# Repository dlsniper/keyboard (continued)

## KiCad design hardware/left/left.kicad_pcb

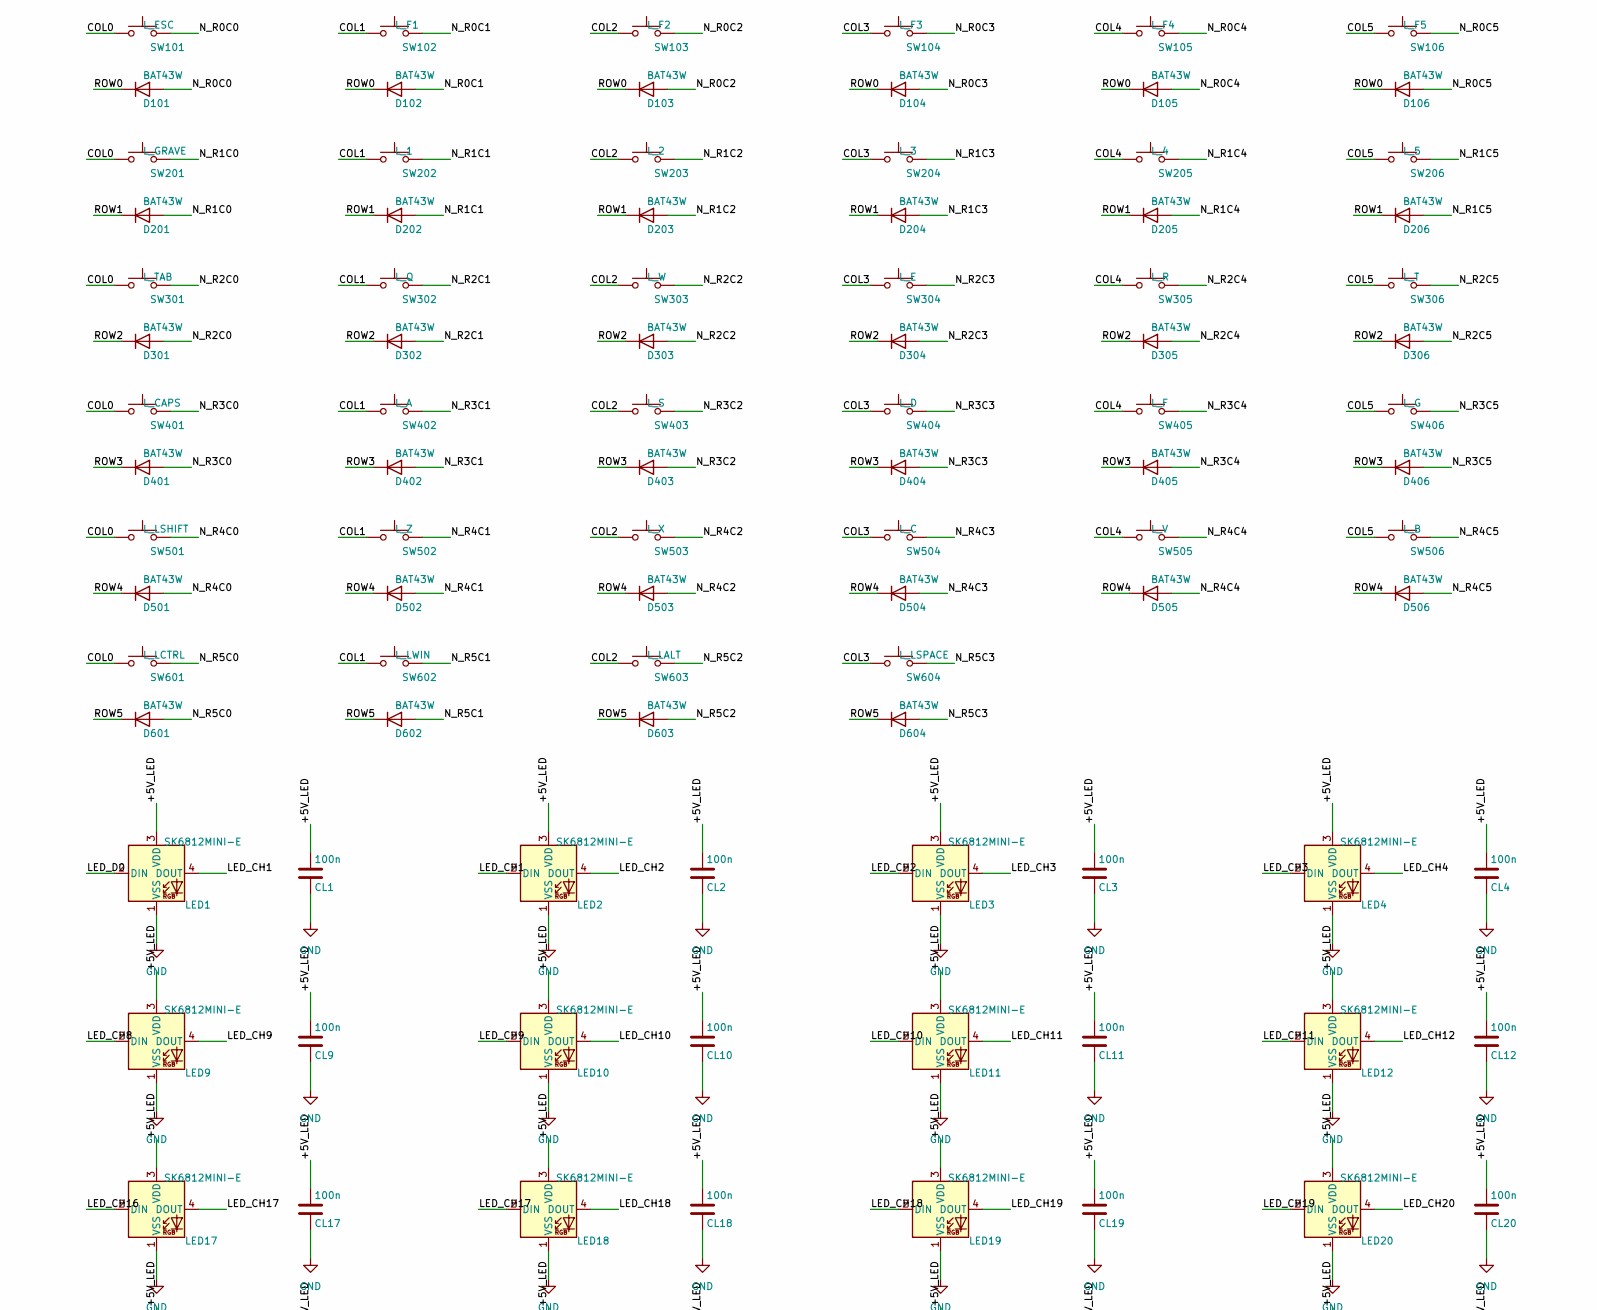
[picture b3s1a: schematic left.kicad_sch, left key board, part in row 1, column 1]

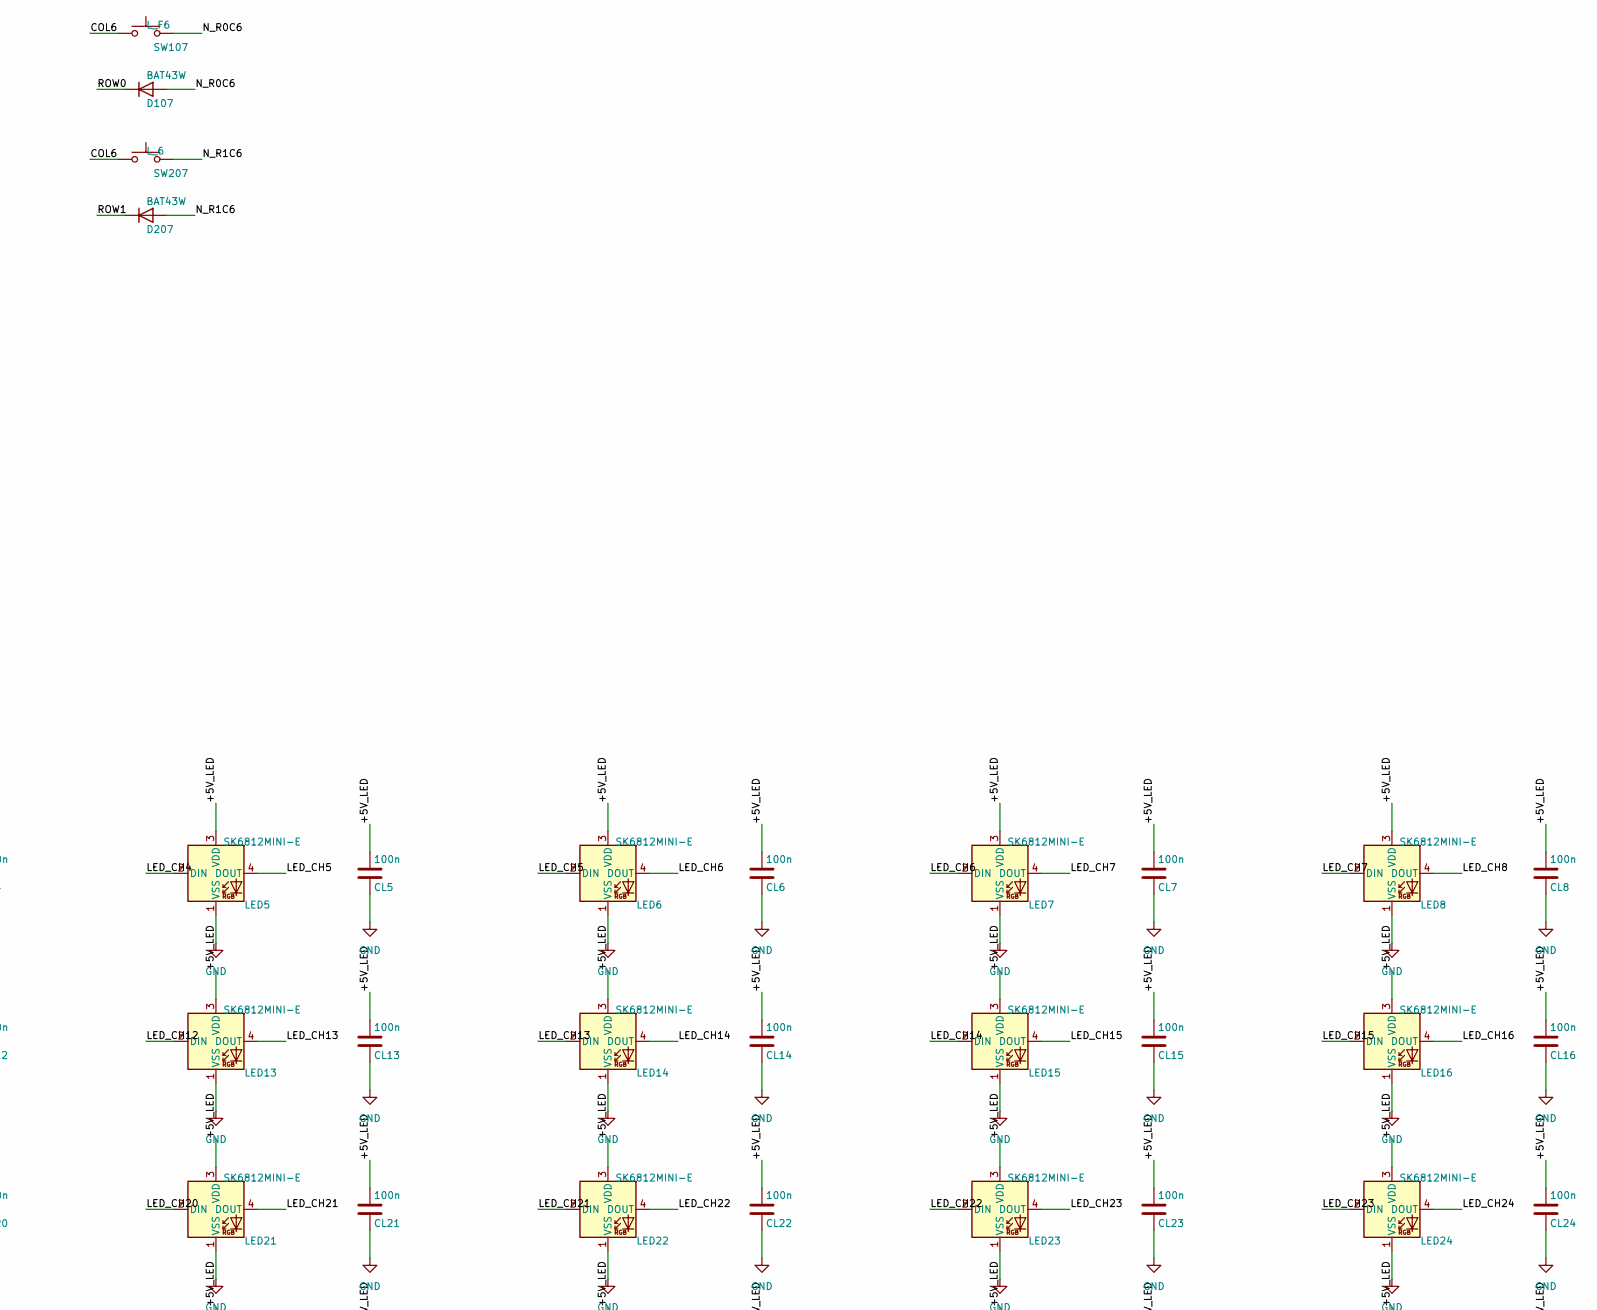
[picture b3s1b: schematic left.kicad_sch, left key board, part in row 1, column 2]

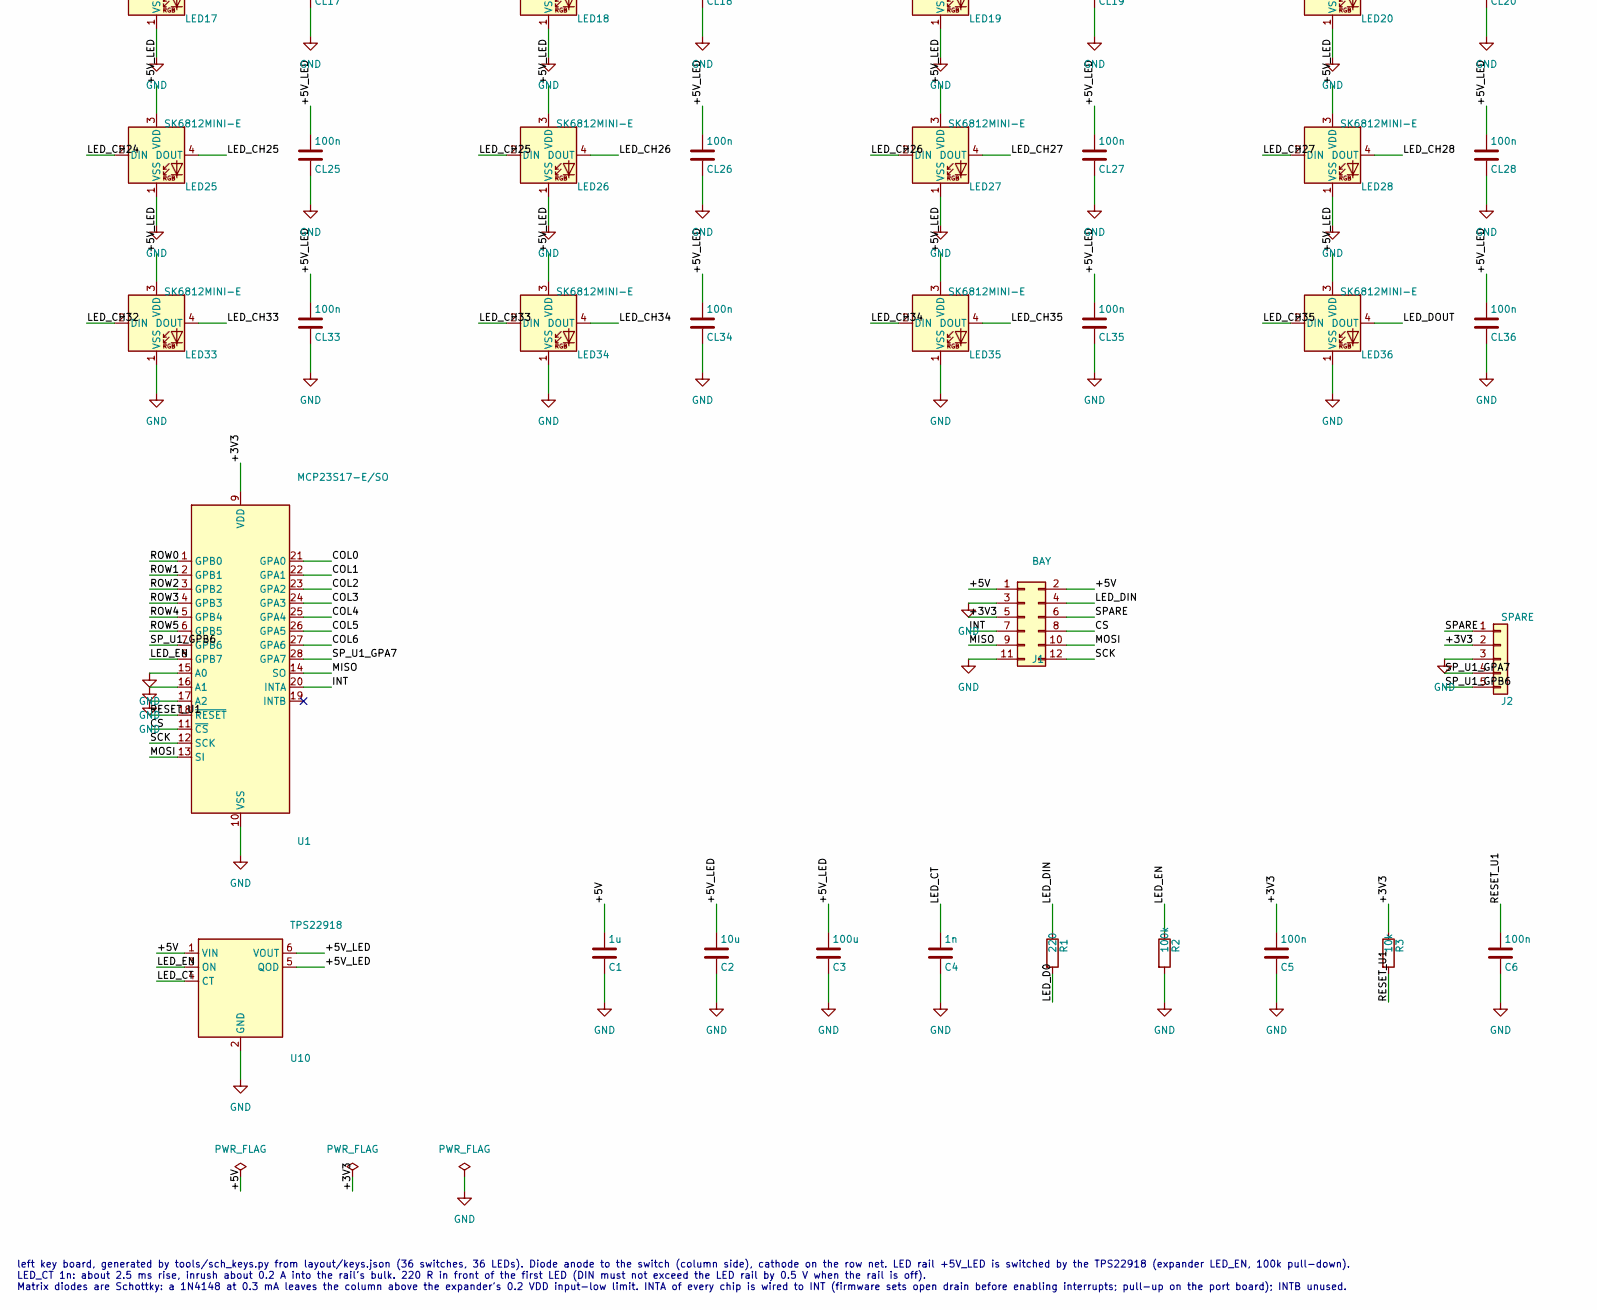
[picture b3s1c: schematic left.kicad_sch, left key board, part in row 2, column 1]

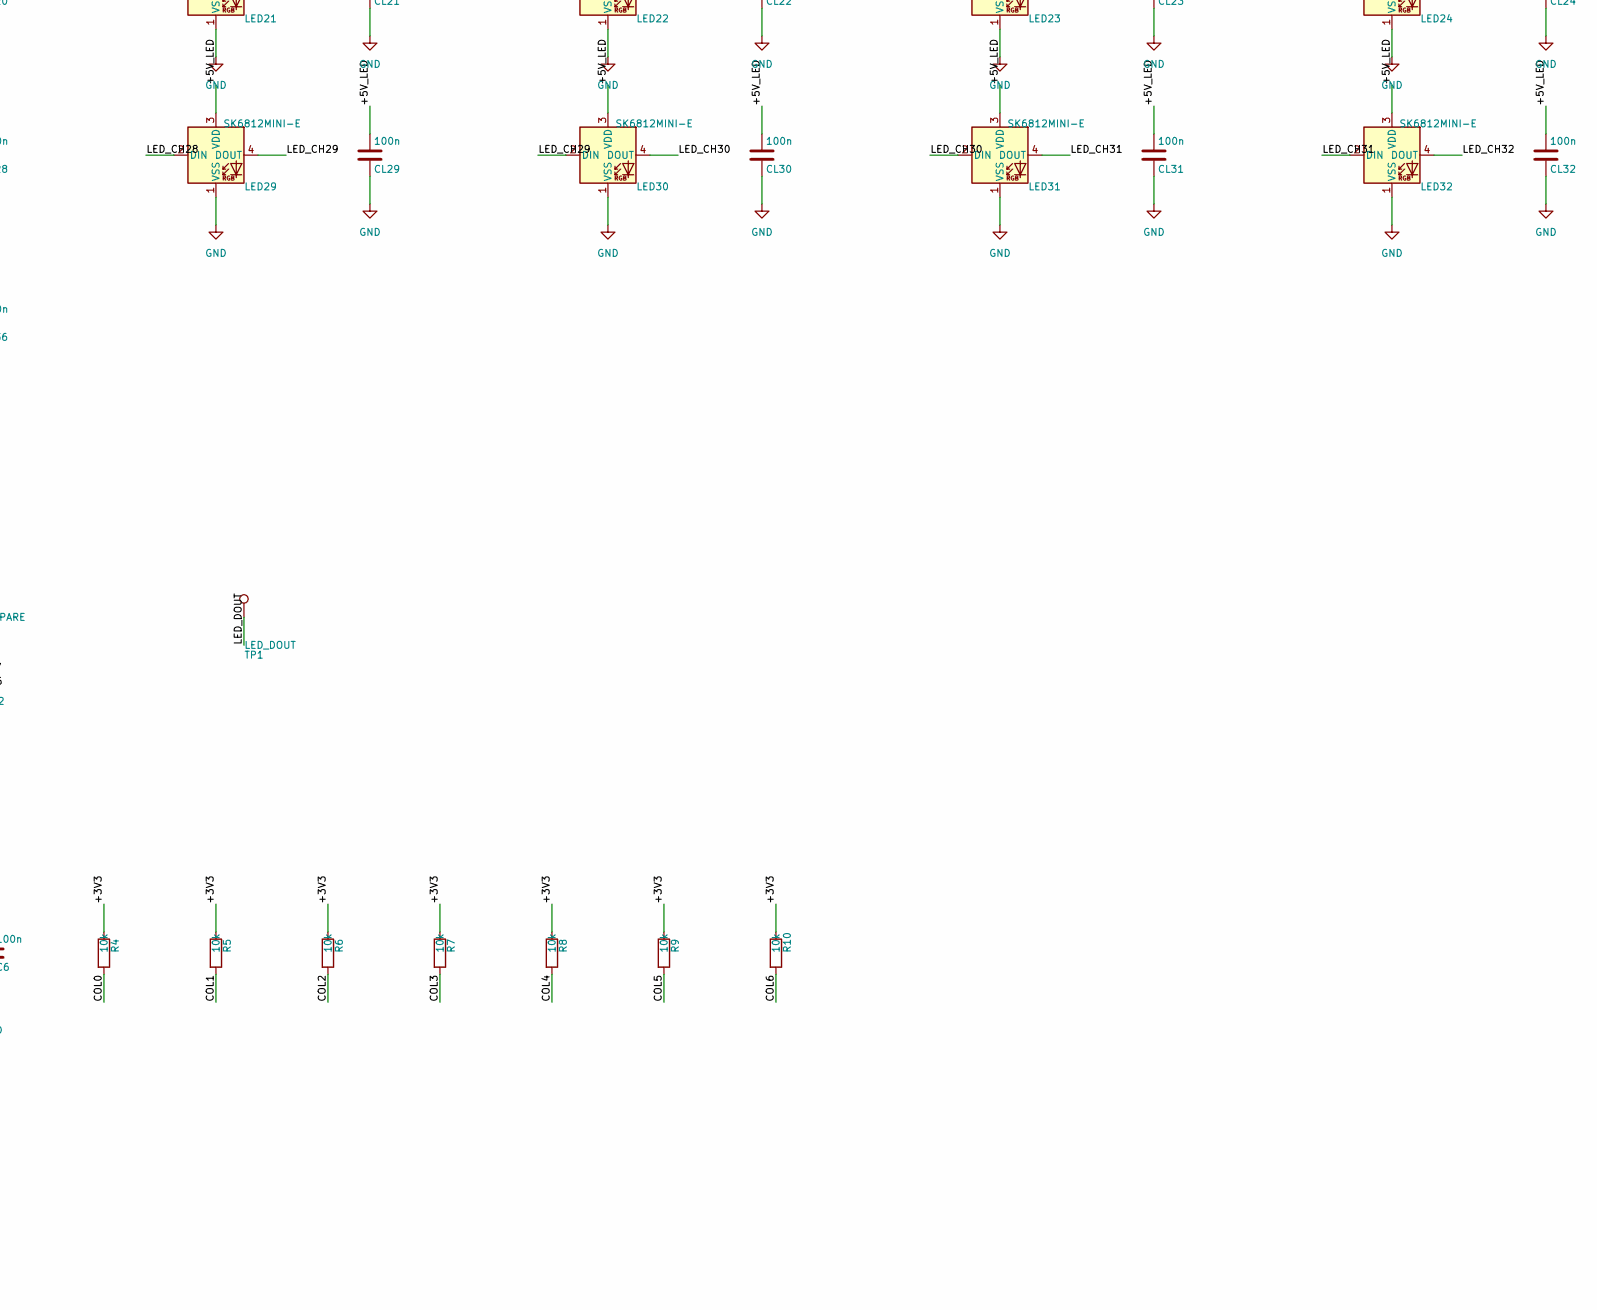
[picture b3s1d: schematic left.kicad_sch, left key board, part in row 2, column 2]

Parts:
C1: 1u; C_0805_2012Metric_Pad1.18x1.45mm_HandSolder; Voltage 16V
C2: 10u; C_0805_2012Metric_Pad1.18x1.45mm_HandSolder; Voltage 16V
C3: 100u; C_1210_3225Metric_Pad1.33x2.70mm_HandSolder; Voltage 10V
C4: 1n; C_0805_2012Metric_Pad1.18x1.45mm_HandSolder; Voltage 16V
C5, C6: 100n; C_0805_2012Metric_Pad1.18x1.45mm_HandSolder; Voltage 16V
CL1, CL2, CL3, CL4, CL5, CL6, CL7, CL8, CL9, CL10, CL11, CL12, CL13, CL14, CL15, CL16, CL17, CL18, CL19, CL20, CL21, CL22, CL23, CL24, CL25, CL26, CL27, CL28, CL29, CL30, CL31, CL32, CL33, CL34, CL35, CL36: 100n; C_0805_2012Metric_Pad1.18x1.45mm_HandSolder; Voltage 16V
D101, D102, D103, D104, D105, D106, D107, D201, D202, D203, D204, D205, D206, D207, D301, D302, D303, D304, D305, D306, D401, D402, D403, D404, D405, D406, D501, D502, D503, D504, D505, D506, D601, D602, D603, D604: BAT43W; D_SOD-123; MPN Schottky, SOD-123: BAT43W (VF 0.33 V ma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
J1: BAY; PinHeader_2x06_P2.54mm_Vertical; MPN generic 2x6 2.54 mm pin header
J2: SPARE; PinHeader_1x05_P2.54mm_Vertical; MPN generic 1xN 2.54 mm pin header
LED1, LED2, LED3, LED4, LED5, LED6, LED7, LED8, LED9, LED10, LED11, LED12, LED13, LED14, LED15, LED16, LED17, LED18, LED19, LED20, LED21, LED22, LED23, LED24, LED25, LED26, LED27, LED28, LED29, LED30, LED31, LED32, LED33, LED34, LED35, LED36: SK6812MINI-E; LED_SK6812MINI-E_3.2x2.8mm_P1.5mm_ReverseMount; MPN SK6812MINI-E
R1: 220; R_0805_2012Metric_Pad1.20x1.40mm_HandSolder; Tolerance 1%
R2: 100k; R_0805_2012Metric_Pad1.20x1.40mm_HandSolder; Tolerance 1%
R3, R4, R5, R6, R7, R8, R9, R10: 10k; R_0805_2012Metric_Pad1.20x1.40mm_HandSolder; Tolerance 1%
SW101: L_ESC; SW_Hotswap_Kailh_MX_1.00u; MPN Kailh CPG151101S11 hotswap socket
SW102: L_F1; SW_Hotswap_Kailh_MX_1.00u; MPN Kailh CPG151101S11 hotswap socket
SW103: L_F2; SW_Hotswap_Kailh_MX_1.00u; MPN Kailh CPG151101S11 hotswap socket
SW104: L_F3; SW_Hotswap_Kailh_MX_1.00u; MPN Kailh CPG151101S11 hotswap socket
SW105: L_F4; SW_Hotswap_Kailh_MX_1.00u; MPN Kailh CPG151101S11 hotswap socket
SW106: L_F5; SW_Hotswap_Kailh_MX_1.00u; MPN Kailh CPG151101S11 hotswap socket
SW107: L_F6; SW_Hotswap_Kailh_MX_1.00u; MPN Kailh CPG151101S11 hotswap socket
SW201: L_GRAVE; SW_Hotswap_Kailh_MX_1.00u; MPN Kailh CPG151101S11 hotswap socket
SW202: L_1; SW_Hotswap_Kailh_MX_1.00u; MPN Kailh CPG151101S11 hotswap socket
SW203: L_2; SW_Hotswap_Kailh_MX_1.00u; MPN Kailh CPG151101S11 hotswap socket
SW204: L_3; SW_Hotswap_Kailh_MX_1.00u; MPN Kailh CPG151101S11 hotswap socket
SW205: L_4; SW_Hotswap_Kailh_MX_1.00u; MPN Kailh CPG151101S11 hotswap socket
SW206: L_5; SW_Hotswap_Kailh_MX_1.00u; MPN Kailh CPG151101S11 hotswap socket
SW207: L_6; SW_Hotswap_Kailh_MX_1.00u; MPN Kailh CPG151101S11 hotswap socket
SW301: L_TAB; SW_Hotswap_Kailh_MX_1.50u; MPN Kailh CPG151101S11 hotswap socket
SW302: L_Q; SW_Hotswap_Kailh_MX_1.00u; MPN Kailh CPG151101S11 hotswap socket
SW303: L_W; SW_Hotswap_Kailh_MX_1.00u; MPN Kailh CPG151101S11 hotswap socket
SW304: L_E; SW_Hotswap_Kailh_MX_1.00u; MPN Kailh CPG151101S11 hotswap socket
SW305: L_R; SW_Hotswap_Kailh_MX_1.00u; MPN Kailh CPG151101S11 hotswap socket
SW306: L_T; SW_Hotswap_Kailh_MX_1.00u; MPN Kailh CPG151101S11 hotswap socket
SW401: L_CAPS; SW_Hotswap_Kailh_MX_1.75u; MPN Kailh CPG151101S11 hotswap socket
SW402: L_A; SW_Hotswap_Kailh_MX_1.00u; MPN Kailh CPG151101S11 hotswap socket
SW403: L_S; SW_Hotswap_Kailh_MX_1.00u; MPN Kailh CPG151101S11 hotswap socket
SW404: L_D; SW_Hotswap_Kailh_MX_1.00u; MPN Kailh CPG151101S11 hotswap socket
SW405: L_F; SW_Hotswap_Kailh_MX_1.00u; MPN Kailh CPG151101S11 hotswap socket
SW406: L_G; SW_Hotswap_Kailh_MX_1.00u; MPN Kailh CPG151101S11 hotswap socket
SW501: L_LSHIFT; SW_Hotswap_Kailh_MX_2.25u; MPN Kailh CPG151101S11 hotswap socket
SW502: L_Z; SW_Hotswap_Kailh_MX_1.00u; MPN Kailh CPG151101S11 hotswap socket
SW503: L_X; SW_Hotswap_Kailh_MX_1.00u; MPN Kailh CPG151101S11 hotswap socket
SW504: L_C; SW_Hotswap_Kailh_MX_1.00u; MPN Kailh CPG151101S11 hotswap socket
SW505: L_V; SW_Hotswap_Kailh_MX_1.00u; MPN Kailh CPG151101S11 hotswap socket
SW506: L_B; SW_Hotswap_Kailh_MX_1.00u; MPN Kailh CPG151101S11 hotswap socket
SW601: L_LCTRL; SW_Hotswap_Kailh_MX_1.50u; MPN Kailh CPG151101S11 hotswap socket
SW602: L_LWIN; SW_Hotswap_Kailh_MX_1.50u; MPN Kailh CPG151101S11 hotswap socket
SW603: L_LALT; SW_Hotswap_Kailh_MX_1.50u; MPN Kailh CPG151101S11 hotswap socket
SW604: L_LSPACE; SW_Hotswap_Kailh_MX_2.75u; MPN Kailh CPG151101S11 hotswap socket
TP1: LED_DOUT; TestPoint_Pad_D1.5mm
U1: MCP23S17-E/SO; SOIC-28W_7.5x17.9mm_P1.27mm; MPN Microchip MCP23S17-E/SO
U10: TPS22918; TI_SOT-23-6_DBV0006A; MPN TI TPS22918DBVR

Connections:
/+3V3: C5.1, J1.5, J2.2, R3.1, R4.1, R5.1, R6.1, R7.1, R8.1, R9.1, R10.1, U1.9 (VDD)
/+5V: C1.1, J1.1, J1.2, U10.1 (VIN)
/+5V_LED: C2.1, C3.1, CL1.1, CL2.1, CL3.1, CL4.1, CL5.1, CL6.1, CL7.1, CL8.1, CL9.1, CL10.1, CL11.1, CL12.1, CL13.1, CL14.1, CL15.1, CL16.1, CL17.1, CL18.1, CL19.1, CL20.1, CL21.1, CL22.1, CL23.1, CL24.1, CL25.1, CL26.1, CL27.1, CL28.1, CL29.1, CL30.1, CL31.1, CL32.1, CL33.1, CL34.1, CL35.1, CL36.1, LED1.3 (VDD), LED2.3 (VDD), LED3.3 (VDD), LED4.3 (VDD), LED5.3 (VDD), LED6.3 (VDD), LED7.3 (VDD), LED8.3 (VDD), LED9.3 (VDD), LED10.3 (VDD), LED11.3 (VDD), LED12.3 (VDD), LED13.3 (VDD), LED14.3 (VDD), LED15.3 (VDD), LED16.3 (VDD), LED17.3 (VDD), LED18.3 (VDD), LED19.3 (VDD), LED20.3 (VDD), LED21.3 (VDD), LED22.3 (VDD), LED23.3 (VDD), LED24.3 (VDD), LED25.3 (VDD), LED26.3 (VDD), LED27.3 (VDD), LED28.3 (VDD), LED29.3 (VDD), LED30.3 (VDD), LED31.3 (VDD), LED32.3 (VDD), LED33.3 (VDD), LED34.3 (VDD), LED35.3 (VDD), LED36.3 (VDD), U10.5 (QOD), U10.6 (VOUT)
/COL0: R4.2, SW101.1, SW201.1, SW301.1, SW401.1, SW501.1, SW601.1, U1.21 (GPA0)
/COL1: R5.2, SW102.1, SW202.1, SW302.1, SW402.1, SW502.1, SW602.1, U1.22 (GPA1)
/COL2: R6.2, SW103.1, SW203.1, SW303.1, SW403.1, SW503.1, SW603.1, U1.23 (GPA2)
/COL3: R7.2, SW104.1, SW204.1, SW304.1, SW404.1, SW504.1, SW604.1, U1.24 (GPA3)
/COL4: R8.2, SW105.1, SW205.1, SW305.1, SW405.1, SW505.1, U1.25 (GPA4)
/COL5: R9.2, SW106.1, SW206.1, SW306.1, SW406.1, SW506.1, U1.26 (GPA5)
/COL6: R10.2, SW107.1, SW207.1, U1.27 (GPA6)
/CS: J1.8, U1.11 (~CS)
/INT: J1.7, U1.20 (INTA)
/LED_CH1: LED1.4 (DOUT), LED2.2 (DIN)
/LED_CH2: LED2.4 (DOUT), LED3.2 (DIN)
/LED_CH3: LED3.4 (DOUT), LED4.2 (DIN)
/LED_CH4: LED4.4 (DOUT), LED5.2 (DIN)
/LED_CH5: LED5.4 (DOUT), LED6.2 (DIN)
/LED_CH6: LED6.4 (DOUT), LED7.2 (DIN)
/LED_CH7: LED7.4 (DOUT), LED8.2 (DIN)
/LED_CH8: LED8.4 (DOUT), LED9.2 (DIN)
/LED_CH9: LED9.4 (DOUT), LED10.2 (DIN)
/LED_CH10: LED10.4 (DOUT), LED11.2 (DIN)
/LED_CH11: LED11.4 (DOUT), LED12.2 (DIN)
/LED_CH12: LED12.4 (DOUT), LED13.2 (DIN)
/LED_CH13: LED13.4 (DOUT), LED14.2 (DIN)
/LED_CH14: LED14.4 (DOUT), LED15.2 (DIN)
/LED_CH15: LED15.4 (DOUT), LED16.2 (DIN)
/LED_CH16: LED16.4 (DOUT), LED17.2 (DIN)
/LED_CH17: LED17.4 (DOUT), LED18.2 (DIN)
/LED_CH18: LED18.4 (DOUT), LED19.2 (DIN)
/LED_CH19: LED19.4 (DOUT), LED20.2 (DIN)
/LED_CH20: LED20.4 (DOUT), LED21.2 (DIN)
/LED_CH21: LED21.4 (DOUT), LED22.2 (DIN)
/LED_CH22: LED22.4 (DOUT), LED23.2 (DIN)
/LED_CH23: LED23.4 (DOUT), LED24.2 (DIN)
/LED_CH24: LED24.4 (DOUT), LED25.2 (DIN)
/LED_CH25: LED25.4 (DOUT), LED26.2 (DIN)
/LED_CH26: LED26.4 (DOUT), LED27.2 (DIN)
/LED_CH27: LED27.4 (DOUT), LED28.2 (DIN)
/LED_CH28: LED28.4 (DOUT), LED29.2 (DIN)
/LED_CH29: LED29.4 (DOUT), LED30.2 (DIN)
/LED_CH30: LED30.4 (DOUT), LED31.2 (DIN)
/LED_CH31: LED31.4 (DOUT), LED32.2 (DIN)
/LED_CH32: LED32.4 (DOUT), LED33.2 (DIN)
/LED_CH33: LED33.4 (DOUT), LED34.2 (DIN)
/LED_CH34: LED34.4 (DOUT), LED35.2 (DIN)
/LED_CH35: LED35.4 (DOUT), LED36.2 (DIN)
/LED_CT: C4.1, U10.4 (CT)
/LED_D0: LED1.2 (DIN), R1.2
/LED_DIN: J1.4, R1.1
/LED_DOUT: LED36.4 (DOUT), TP1.1
/LED_EN: R2.1, U1.8 (GPB7), U10.3 (ON)
/MISO: J1.9, U1.14 (SO)
/MOSI: J1.10, U1.13 (SI)
/N_R0C0: D101.2 (A), SW101.2
/N_R0C1: D102.2 (A), SW102.2
/N_R0C2: D103.2 (A), SW103.2
/N_R0C3: D104.2 (A), SW104.2
/N_R0C4: D105.2 (A), SW105.2
/N_R0C5: D106.2 (A), SW106.2
/N_R0C6: D107.2 (A), SW107.2
/N_R1C0: D201.2 (A), SW201.2
/N_R1C1: D202.2 (A), SW202.2
/N_R1C2: D203.2 (A), SW203.2
/N_R1C3: D204.2 (A), SW204.2
/N_R1C4: D205.2 (A), SW205.2
/N_R1C5: D206.2 (A), SW206.2
/N_R1C6: D207.2 (A), SW207.2
/N_R2C0: D301.2 (A), SW301.2
/N_R2C1: D302.2 (A), SW302.2
/N_R2C2: D303.2 (A), SW303.2
/N_R2C3: D304.2 (A), SW304.2
/N_R2C4: D305.2 (A), SW305.2
/N_R2C5: D306.2 (A), SW306.2
/N_R3C0: D401.2 (A), SW401.2
/N_R3C1: D402.2 (A), SW402.2
/N_R3C2: D403.2 (A), SW403.2
/N_R3C3: D404.2 (A), SW404.2
/N_R3C4: D405.2 (A), SW405.2
/N_R3C5: D406.2 (A), SW406.2
/N_R4C0: D501.2 (A), SW501.2
/N_R4C1: D502.2 (A), SW502.2
/N_R4C2: D503.2 (A), SW503.2
/N_R4C3: D504.2 (A), SW504.2
/N_R4C4: D505.2 (A), SW505.2
/N_R4C5: D506.2 (A), SW506.2
/N_R5C0: D601.2 (A), SW601.2
/N_R5C1: D602.2 (A), SW602.2
/N_R5C2: D603.2 (A), SW603.2
/N_R5C3: D604.2 (A), SW604.2
/RESET_U1: C6.1, R3.2, U1.18 (~RESET)
/ROW0: D101.1 (K), D102.1 (K), D103.1 (K), D104.1 (K), D105.1 (K), D106.1 (K), D107.1 (K), U1.1 (GPB0)
/ROW1: D201.1 (K), D202.1 (K), D203.1 (K), D204.1 (K), D205.1 (K), D206.1 (K), D207.1 (K), U1.2 (GPB1)
/ROW2: D301.1 (K), D302.1 (K), D303.1 (K), D304.1 (K), D305.1 (K), D306.1 (K), U1.3 (GPB2)
/ROW3: D401.1 (K), D402.1 (K), D403.1 (K), D404.1 (K), D405.1 (K), D406.1 (K), U1.4 (GPB3)
/ROW4: D501.1 (K), D502.1 (K), D503.1 (K), D504.1 (K), D505.1 (K), D506.1 (K), U1.5 (GPB4)
/ROW5: D601.1 (K), D602.1 (K), D603.1 (K), D604.1 (K), U1.6 (GPB5)
/SCK: J1.12, U1.12 (SCK)
/SPARE: J1.6, J2.1
/SP_U1_GPA7: J2.4, U1.28 (GPA7)
/SP_U1_GPB6: J2.5, U1.7 (GPB6)
GND: C1.2, C2.2, C3.2, C4.2, C5.2, C6.2, CL1.2, CL2.2, CL3.2, CL4.2, CL5.2, CL6.2, CL7.2, CL8.2, CL9.2, CL10.2, CL11.2, CL12.2, CL13.2, CL14.2, CL15.2, CL16.2, CL17.2, CL18.2, CL19.2, CL20.2, CL21.2, CL22.2, CL23.2, CL24.2, CL25.2, CL26.2, CL27.2, CL28.2, CL29.2, CL30.2, CL31.2, CL32.2, CL33.2, CL34.2, CL35.2, CL36.2, J1.3, J1.11, J2.3, LED1.1 (VSS), LED2.1 (VSS), LED3.1 (VSS), LED4.1 (VSS), LED5.1 (VSS), LED6.1 (VSS), LED7.1 (VSS), LED8.1 (VSS), LED9.1 (VSS), LED10.1 (VSS), LED11.1 (VSS), LED12.1 (VSS), LED13.1 (VSS), LED14.1 (VSS), LED15.1 (VSS), LED16.1 (VSS), LED17.1 (VSS), LED18.1 (VSS), LED19.1 (VSS), LED20.1 (VSS), LED21.1 (VSS), LED22.1 (VSS), LED23.1 (VSS), LED24.1 (VSS), LED25.1 (VSS), LED26.1 (VSS), LED27.1 (VSS), LED28.1 (VSS), LED29.1 (VSS), LED30.1 (VSS), LED31.1 (VSS), LED32.1 (VSS), LED33.1 (VSS), LED34.1 (VSS), LED35.1 (VSS), LED36.1 (VSS), R2.2, U1.10 (VSS), U1.15 (A0), U1.16 (A1), U1.17 (A2), U10.2 (GND)

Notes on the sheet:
left key board, generated by tools/sch_keys.py from layout/keys.json (36 switches, 36 LEDs). Diode anode to the switch (column side), cathode on the row net. LED rail +5V_LED is switched by the TPS22918 (expander LED_EN, 100k pull-down). LED_CT 1n: about 2.5 ms rise, inrush about 0.2 A into the rai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

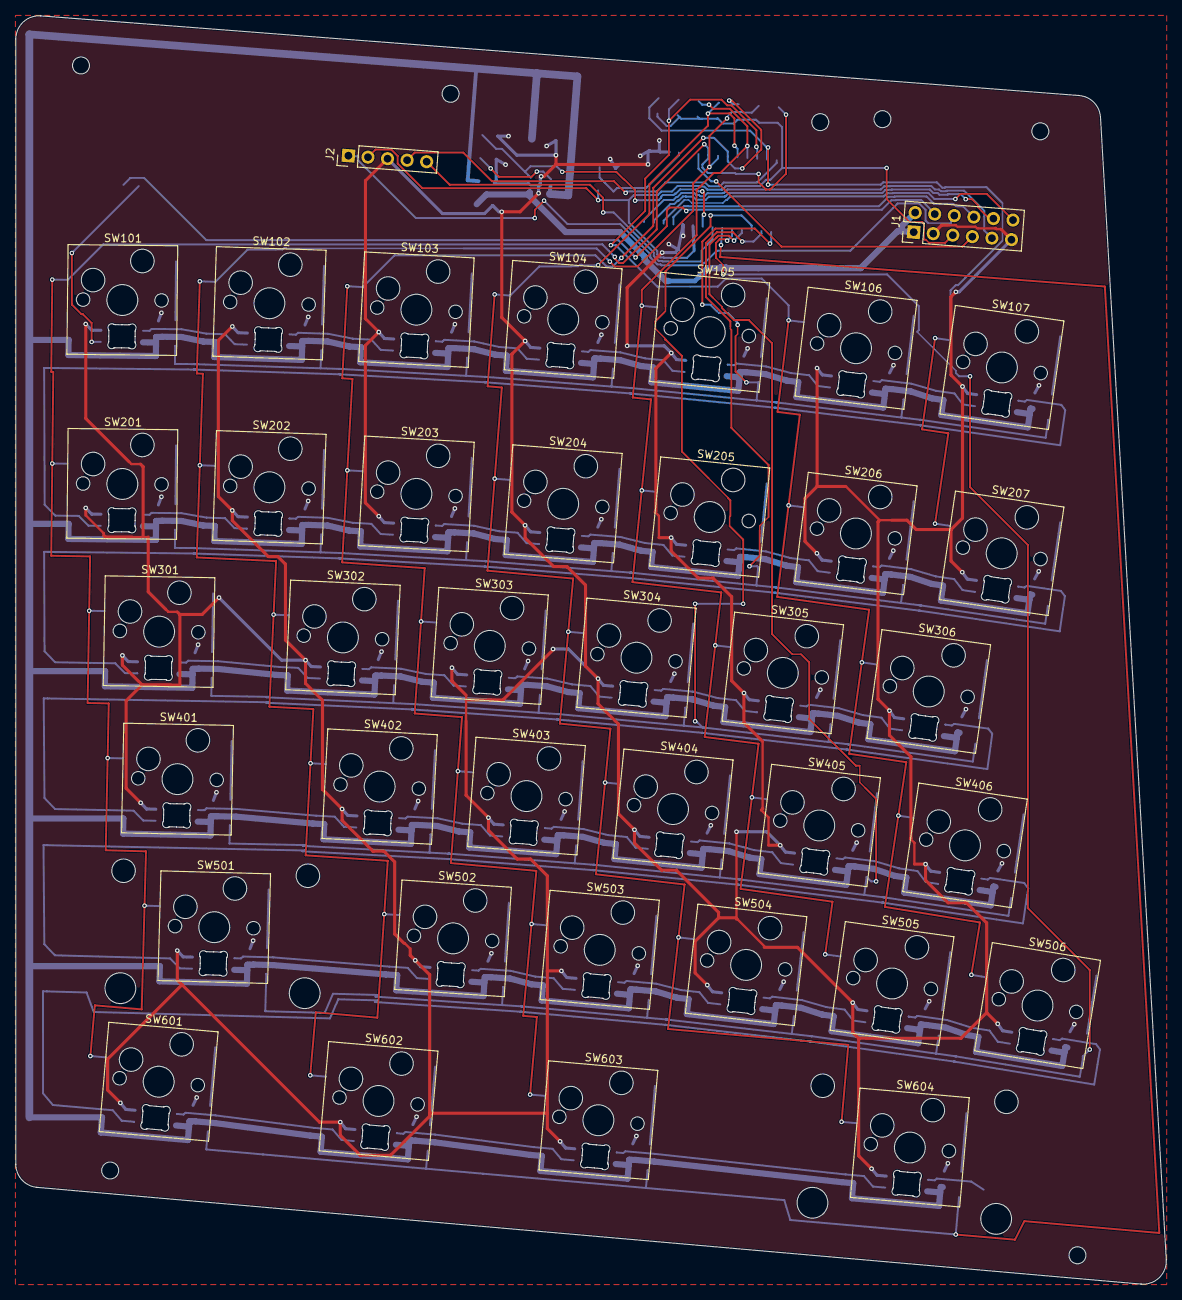
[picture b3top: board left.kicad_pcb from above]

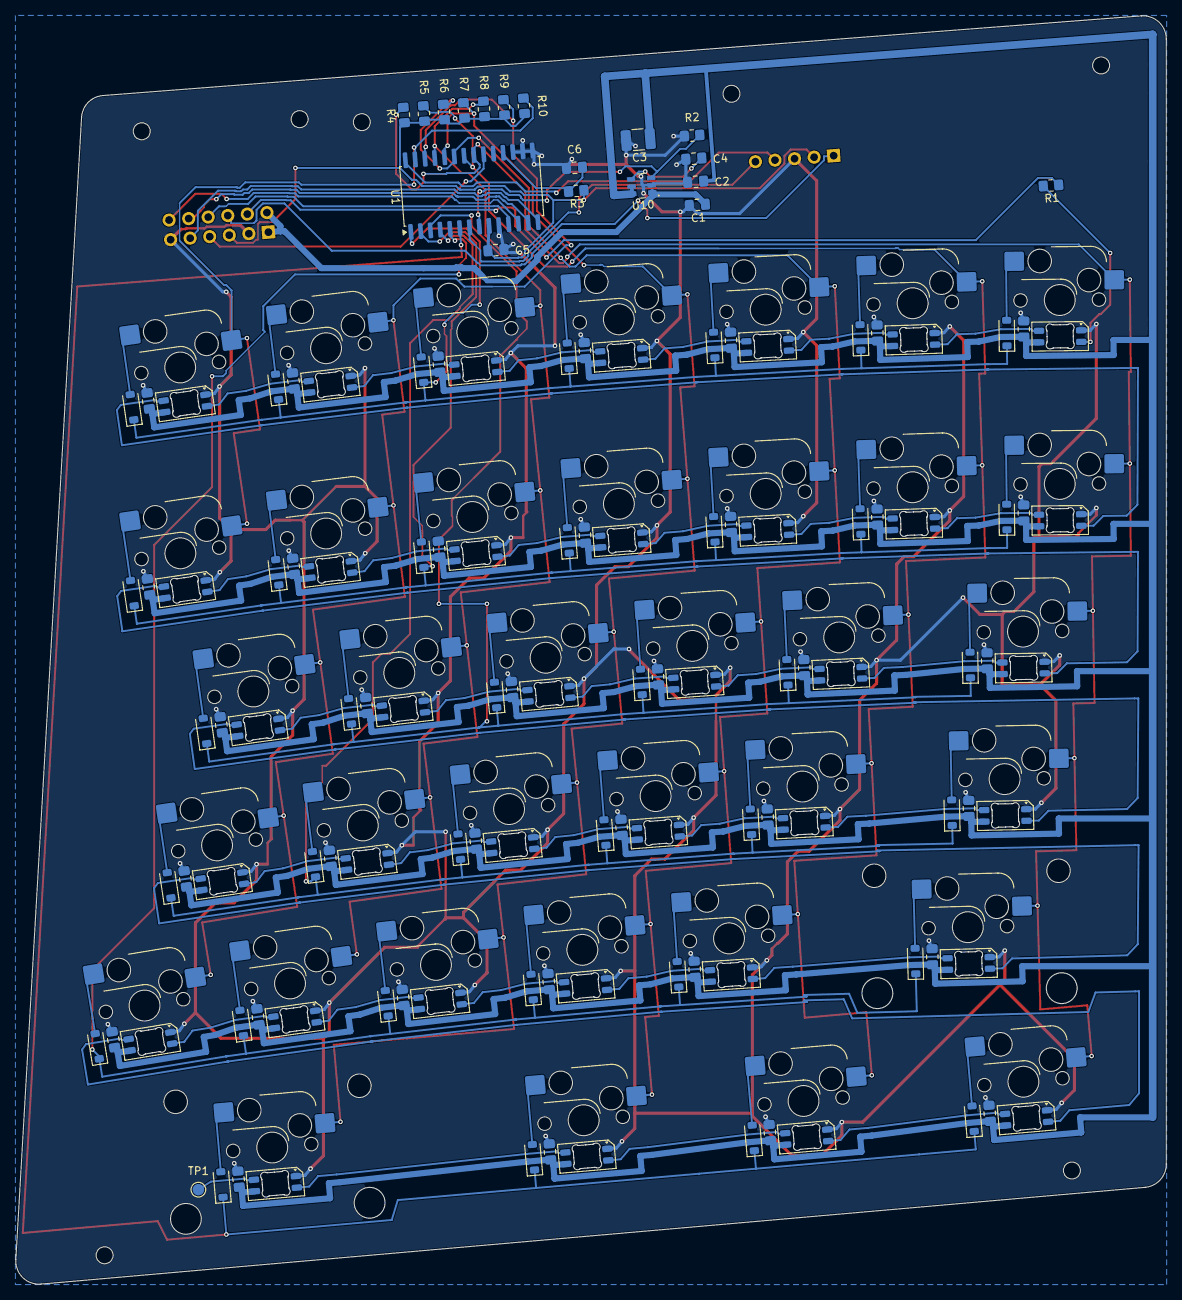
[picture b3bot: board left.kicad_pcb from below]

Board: 2 copper layers, 148.9 x 164.2 mm, 174 parts (127 on the bottom side), 102 nets.

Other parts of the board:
H3, H4, H5, H6, H7, H8, H9: MountingHole_2.2mm_M2
ST1, ST2: Stabilizer_Cherry_MX_2.00u
